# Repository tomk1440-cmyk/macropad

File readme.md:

#  **Pacropad**

### Features:
- 9 Cherry MX Keys
- 1 EC11 Rotary Encoder
- Seed Xiao RP2048
- USB C Support
- Glue-On Case
  
### The PCB

This picture shows how the pcb looks in 3D view in KiCad
PCB itself was made in kicad

### **Case**
-Case is divided into 2 parts top and bottom

top part:

bottom part:

**Firmware:**

This project uses QMK firmware.

**BOM:**

Bill Of Materials (BOM) is availible in /bom/bom.zip

### Open-Source macropad for apps and games
as a total noob, i think i did it fairly well.
This repo and project was made by a 14 year old student from Czech Republic
Who is this repo made for?
- For someone searching for open source pcb with case and all schematic
- For curious persons
- Basically for everyone.
You can check the demo of the case on Youtube on channel Glixie.
Why was Pacropad made?
- I wanted to make my own pcb
- It was a Stardance mission
- It is tuff
- I want to get better at making PCB's in the future 

This project is part of HackClub Stardance
Check it out here: https://stardance.hackclub.com/projects/47211
you can follow me on:

instagram: @_potipek_

tiktok: @Czpotipek

youtube: @CZGlixie

Thank you for checking out my repo
### **This project and repo is open-source**
### **Feel free to check out my other projects!**
### firmware should be final

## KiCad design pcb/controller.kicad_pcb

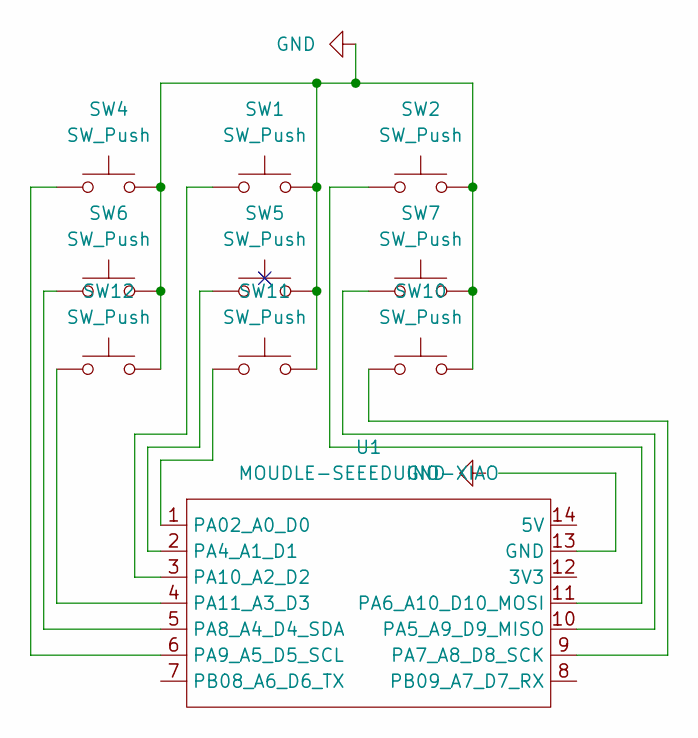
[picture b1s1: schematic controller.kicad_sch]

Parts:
SW1, SW2, SW4, SW5, SW6, SW7, SW10, SW11, SW12: SW_Push; SW_Cherry_MX_1.00u_PCB
U1: MOUDLE-SEEEDUINO-XIAO; XIAO-Generic-Hybrid-14P-2.54-21X17.8MM

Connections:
GND: SW1.2, SW2.2, SW4.2, SW5.2, SW6.2, SW7.2, SW10.2, SW11.2, SW12.2, U1.13 (GND); also elsewhere on the board
unnamed: SW11.1, U1.1 (PA02_A0_D0)
unnamed: SW5.1, U1.2 (PA4_A1_D1)
unnamed: SW7.1, U1.10 (PA5_A9_D9_MISO)
unnamed: SW2.1, U1.11 (PA6_A10_D10_MOSI)
unnamed: SW10.1, U1.9 (PA7_A8_D8_SCK)
unnamed: SW6.1, U1.5 (PA8_A4_D4_SDA)
unnamed: SW4.1, U1.6 (PA9_A5_D5_SCL)
unnamed: SW1.1, U1.3 (PA10_A2_D2)
unnamed: SW12.1, U1.4 (PA11_A3_D3)
unnamed 10: U1.7 (PB08_A6_D6_TX); also elsewhere on the board
unnamed 11: U1.8 (PB09_A7_D7_RX); also elsewhere on the board

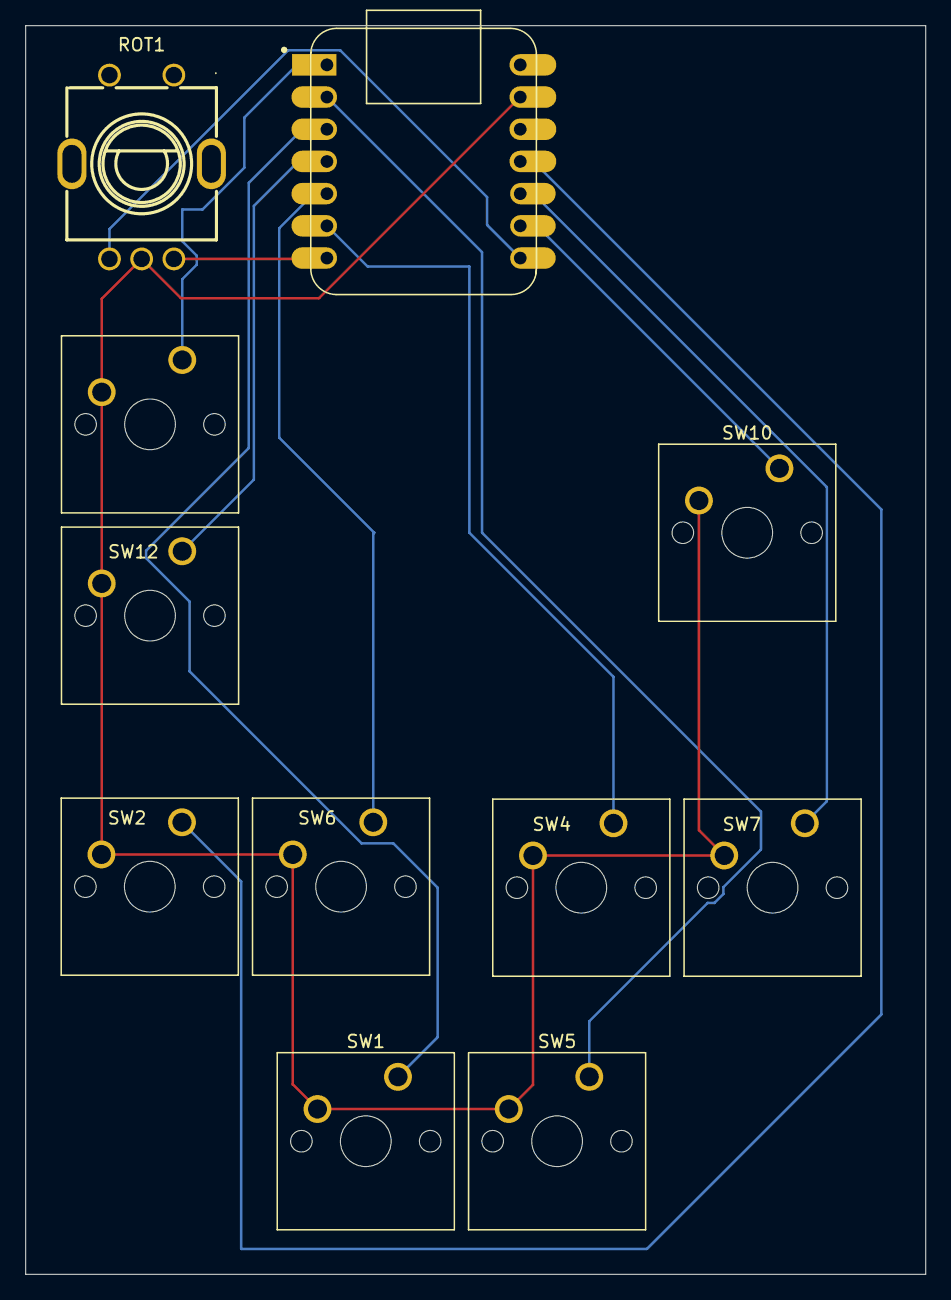
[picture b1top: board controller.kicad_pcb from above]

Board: 2 copper layers, 71.0 x 98.5 mm, 11 parts (0 on the bottom side), 12 nets.

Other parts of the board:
ROT1: EC11E15244G1; SW-TH_EC11E15244G1

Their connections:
GND: ROT1.C; also elsewhere on the board
unnamed 10: ROT1.B; also elsewhere on the board
unnamed 11: ROT1.A; also elsewhere on the board
